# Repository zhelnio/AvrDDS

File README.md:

# AvrDDS
ATmega88 based DDS signal generator from 2013

Old. Simple. And almost without analog part. One of my first AVR devices. It was constructed before I had passed 
[MIT 6.002](https://ocw.mit.edu/courses/electrical-engineering-and-computer-science/6-002-circuits-and-electronics-spring-2007/index.htm) 
course. Published here as an artifact of my home made electronics.

**Schematic**

**Board**

**Menu**

")
")
")
")

**Video of its work**

Originaly published on https://bitbucket.org/zhelnio/avrdds/

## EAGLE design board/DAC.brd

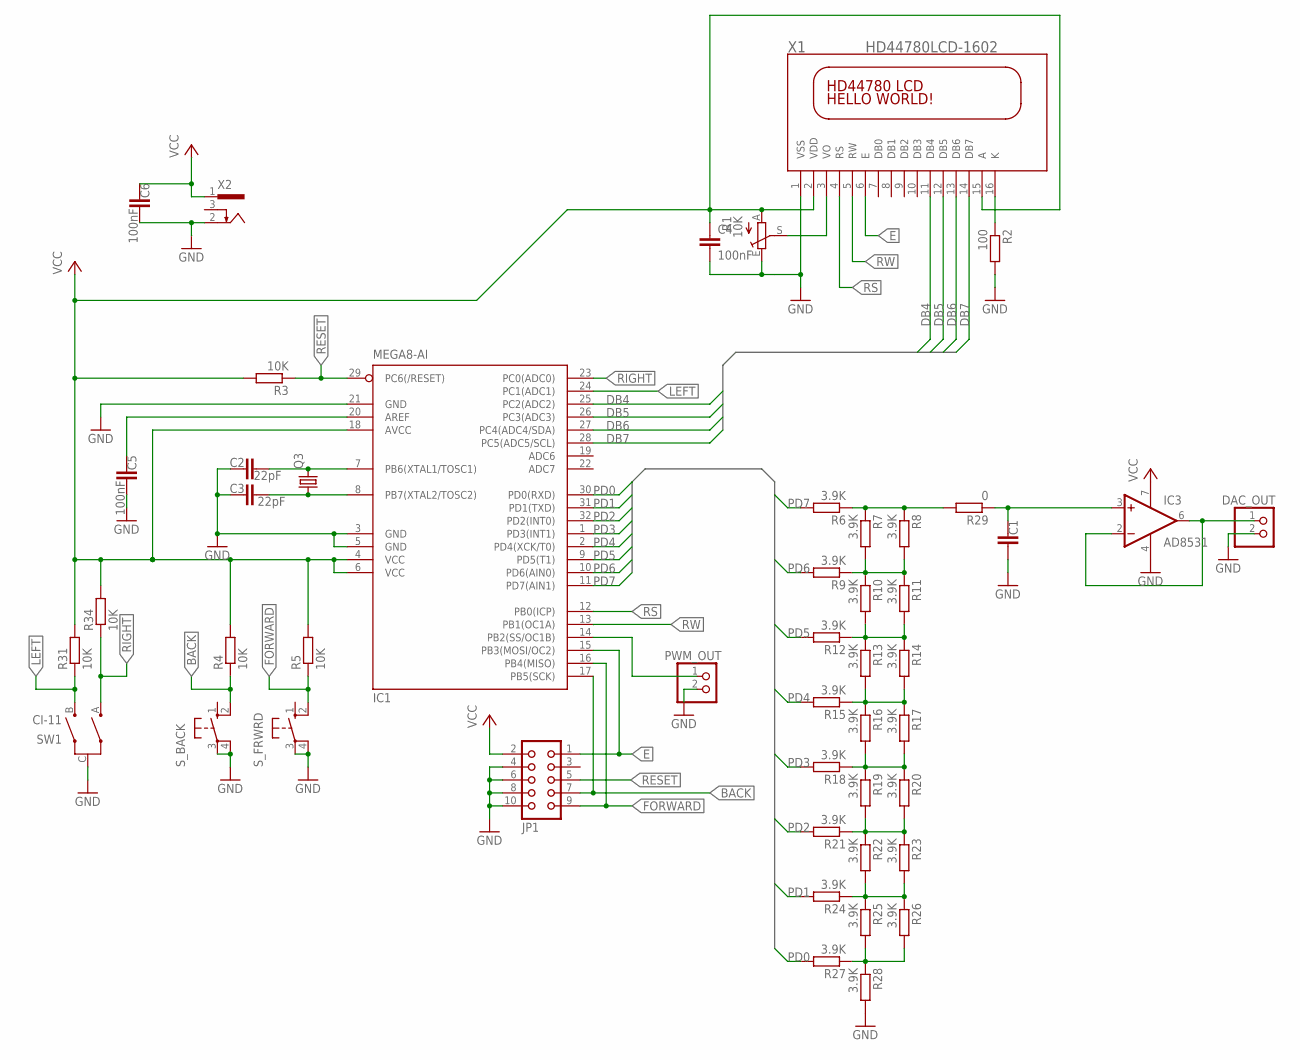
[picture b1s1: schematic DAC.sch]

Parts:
C1: C-EUC1206; C1206
C2, C3: 22pF; C1206
C4, C5, C6: 100nF; C1206
DAC_OUT: PINHD-1X2_2.54-90°; 1X02/90
IC1: MEGA8-AI; TQFP32-08
IC3: AD8531; SO08
JP1: CON10L
PWM_OUT: PINHD-1X2_2.54-90°; 1X02/90
Q3: CRYSTALHC49U-V; HC49U-V
R1: 10K; CA6V
R2: 100; R1206
R3, R4, R5, R31, R34: 10K; R1206
R6, R7, R8, R9, R10, R11, R12, R13, R14, R15, R16, R17, R18, R19, R20, R21, R22, R23, R24, R25, R26, R27, R28: 3.9K; R1206
R29: 0; R1206
SW1: CI-11
S_BACK: 10-XX; B3F-10XX
S_FRWRD: 10-XX; B3F-10XX
X1: HD44780LCD-1602; LCD1602
X2: 733989-5

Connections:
BACK: IC1.17 (PB5(SCK)), JP1.7, R4.1, S_BACK.2 (S1)
DB4: IC1.25 (PC2(ADC2)), X1.11 (DB4)
DB5: IC1.26 (PC3(ADC3)), X1.12 (DB5)
DB6: IC1.27 (PC4(ADC4/SDA)), X1.13 (DB6)
DB7: IC1.28 (PC5(ADC5/SCL)), X1.14 (DB7)
E: IC1.15 (PB3(MOSI/OC2)), JP1.1, X1.6 (E)
FORWARD: IC1.16 (PB4(MISO)), JP1.9, R5.1, S_FRWRD.2 (S1)
GND: C1.2, C2.1, C3.1, C4.2, C5.2, C6.2, DAC_OUT.2, IC1.3 (GND), IC1.5 (GND), IC1.21 (GND), IC3.4 (V-), JP1.4, JP1.6, JP1.8, JP1.10, PWM_OUT.2, R1.E, R2.2, R28.2, SW1.C, S_BACK.3, S_BACK.4 (P1), S_FRWRD.3, S_FRWRD.4 (P1), X1.1 (VSS), X2.2
LEFT: IC1.24 (PC1(ADC1)), R31.1, SW1.B
unnamed: DAC_OUT.1, IC3.2 (-IN), IC3.6 (OUT)
unnamed: C5.1, IC1.20 (AREF)
unnamed: C2.2, IC1.7 (PB6(XTAL1/TOSC1)), Q3.2
unnamed: R1.S, X1.3 (VO)
unnamed: R6.1, R7.1, R8.1, R29.2
unnamed: IC1.14 (PB2(SS/OC1B)), PWM_OUT.1
unnamed: R2.1, X1.16 (K)
unnamed: R7.2, R8.2, R9.1, R10.1, R11.1
unnamed: R10.2, R11.2, R12.1, R13.1, R14.1
unnamed: R13.2, R14.2, R15.1, R16.1, R17.1
unnamed: R16.2, R17.2, R18.1, R19.1, R20.1
unnamed: R19.2, R20.2, R21.1, R22.1, R23.1
unnamed: R22.2, R23.2, R24.1, R25.1, R26.1
unnamed: R25.2, R26.2, R27.1, R28.1
unnamed: C1.1, IC3.3 (+IN), R29.1
unnamed: C3.2, IC1.8 (PB7(XTAL2/TOSC2)), Q3.1
PD0: IC1.30 (PD0(RXD)), R27.2
PD1: IC1.31 (PD1(TXD)), R24.2
PD2: IC1.32 (PD2(INT0)), R21.2
PD3: IC1.1 (PD3(INT1)), R18.2
PD4: IC1.2 (PD4(XCK/T0)), R15.2
PD5: IC1.9 (PD5(T1)), R12.2
PD6: IC1.10 (PD6(AIN0)), R9.2
PD7: IC1.11 (PD7(AIN1)), R6.2
RESET: IC1.29 (PC6(/RESET)), JP1.5, R3.1
RIGHT: IC1.23 (PC0(ADC0)), R34.1, SW1.A
RS: IC1.12 (PB0(ICP)), X1.4 (RS)
RW: IC1.13 (PB1(OC1A)), X1.5 (RW)
VCC: C4.1, C6.1, IC1.4 (VCC), IC1.6 (VCC), IC1.18 (AVCC), IC3.7 (V+), JP1.2, R1.A, R3.2, R4.2, R5.2, R31.2, R34.2, X1.2 (VDD), X1.15 (A), X2.1

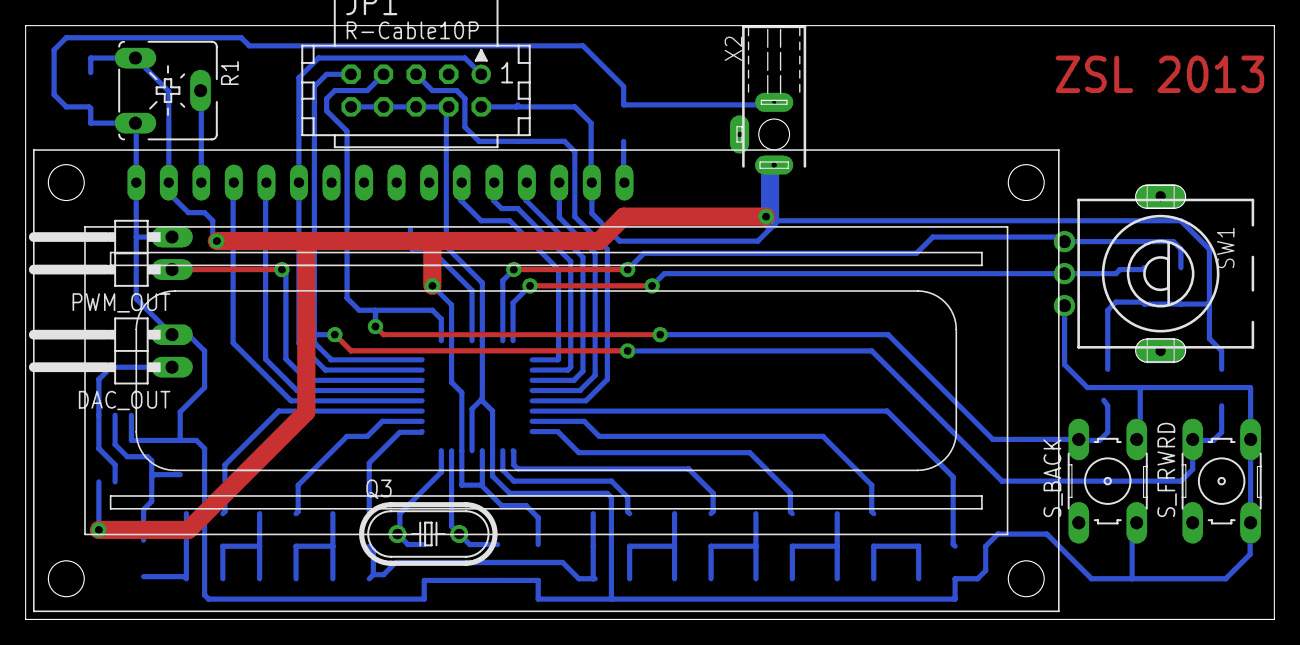
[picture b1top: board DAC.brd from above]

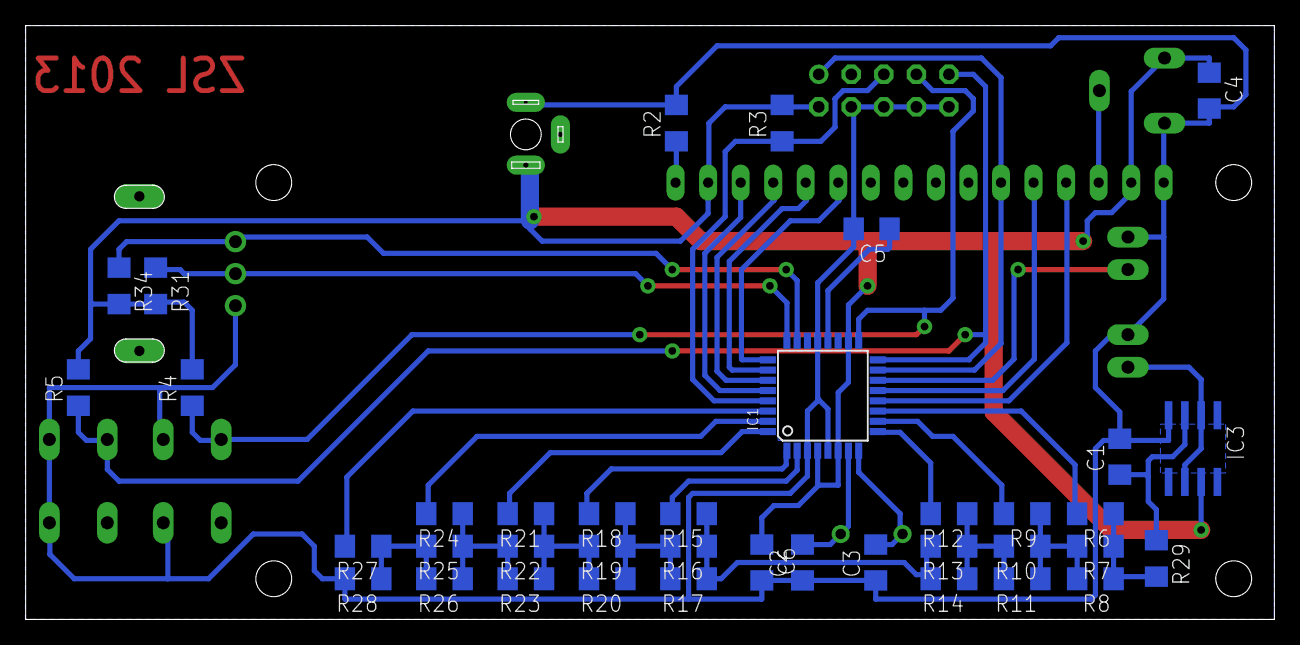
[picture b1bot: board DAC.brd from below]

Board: 2 copper layers, 97.5 x 46.3 mm, 48 parts (38 on the bottom side), 38 nets.

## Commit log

2017-06-30 :confetti_ball: Added .gitattributes & .gitignore files
2017-06-30 firmware source
2017-06-30 hardware schematic
2017-06-30 images added
2017-06-30 image resize
2017-06-30 Create LICENSE
2017-06-30 charset update
